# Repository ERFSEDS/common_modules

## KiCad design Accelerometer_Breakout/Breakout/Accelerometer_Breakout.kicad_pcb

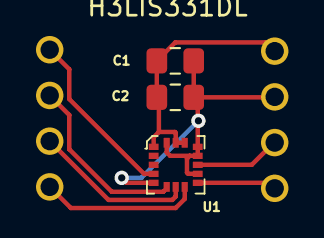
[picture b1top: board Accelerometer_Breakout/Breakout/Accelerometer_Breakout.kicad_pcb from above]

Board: 2 copper layers, 5 parts (0 on the bottom side), 8 nets.

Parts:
C1: 10uF; C_0805_2012Metric_Pad1.15x1.40mm_HandSolder
C2: 0.1uF; C_0805_2012Metric_Pad1.15x1.40mm_HandSolder
U1: H3LIS331DL; TFLGA-16_3x3mm
U2, U3: 4_Pin_header; 4_Pin_Header

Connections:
GND: C1.1, C2.1, U1.5, U1.10, U1.12, U1.13, U1.16, U3.3
unnamed: C1.2, C2.2, U1.1, U1.14, U1.15, U3.4
unnamed: U1.4, U2.1
unnamed: U1.6, U2.2
unnamed: U1.7, U2.3
unnamed: U1.8, U2.4
unnamed: U1.9, U3.1
unnamed: U1.11, U3.2

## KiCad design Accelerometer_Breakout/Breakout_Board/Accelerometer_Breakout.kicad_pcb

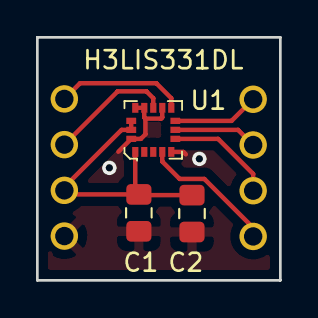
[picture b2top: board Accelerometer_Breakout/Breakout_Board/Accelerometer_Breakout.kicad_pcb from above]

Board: 2 copper layers, 13.5 x 13.5 mm, 5 parts (0 on the bottom side), 8 nets.

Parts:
C1: 10uf; C_0805_2012Metric_Pad1.15x1.40mm_HandSolder
C2: 0.1uf; C_0805_2012Metric_Pad1.15x1.40mm_HandSolder
U1: H3LIS331DL; TFLGA-16_3x3mm
U2, U3: 4_Pin_header; 4_Pin_Header

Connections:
+3V3: C1.1, C2.2, U1.1, U1.14, U1.15, U2.3
/H3LIS331DL_Accelerometer/CS_ACC: U1.8, U3.4
/H3LIS331DL_Accelerometer/INT_1_ACC: U1.11, U2.2
/H3LIS331DL_Accelerometer/INT_2_ACC: U1.9, U2.1
/H3LIS331DL_Accelerometer/SCL_ACC: U1.4, U3.1
/H3LIS331DL_Accelerometer/SDA_ACC: U1.6, U3.2
/H3LIS331DL_Accelerometer/SDO_ACC: U1.7, U3.3
GND: C1.2, C2.1, U1.5, U1.10, U1.12, U1.13, U1.16, U2.4

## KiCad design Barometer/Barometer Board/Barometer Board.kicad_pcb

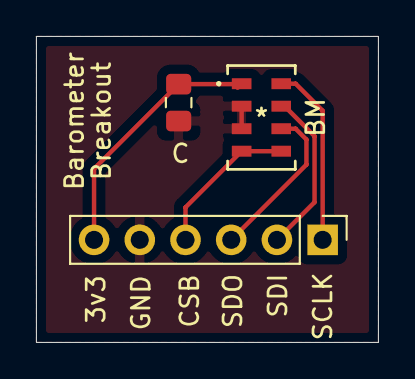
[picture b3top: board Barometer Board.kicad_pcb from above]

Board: 2 copper layers, 19.0 x 17.0 mm, 3 parts (0 on the bottom side), 6 nets.

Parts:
BM: MS560702BA03-50
C: 100nF; C_0805_2012Metric_Pad1.15x1.40mm_HandSolder
Header-Pins301: Conn_01x06_Male; PinHeader_1x06_P2.54mm_Vertical

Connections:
+3V3: BM.1, C.1, Header-Pins301.6
/Barometer/CSB: BM.4, BM.5, Header-Pins301.4
/Barometer/SCLK: BM.8, Header-Pins301.1
/Barometer/SDI: BM.7, Header-Pins301.2
/Barometer/SDO: BM.6, Header-Pins301.3
GND: BM.2, BM.3, C.2, Header-Pins301.5

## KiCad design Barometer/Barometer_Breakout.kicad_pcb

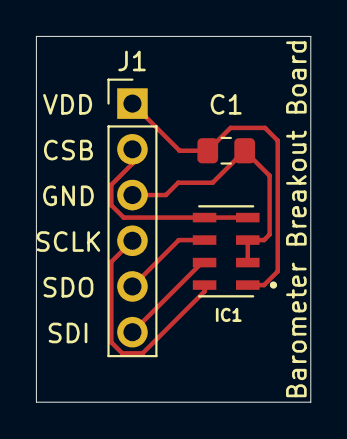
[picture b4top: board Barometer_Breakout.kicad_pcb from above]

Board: 2 copper layers, 15.2 x 20.3 mm, 3 parts (0 on the bottom side), 6 nets.

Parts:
C1: 100nF; C_0805_2012Metric_Pad1.15x1.40mm_HandSolder
IC1: MS560702BA03-50; SON125P300X500X100-8N
J1: Conn_01x06_Male; PinHeader_1x06_P2.54mm_Vertical

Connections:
unnamed: C1.1, IC1.2, IC1.3, J1.3
unnamed: C1.2, IC1.1, J1.1
unnamed: IC1.4, IC1.5, J1.2
unnamed: IC1.8, J1.4
unnamed: IC1.6, J1.5
unnamed: IC1.7, J1.6

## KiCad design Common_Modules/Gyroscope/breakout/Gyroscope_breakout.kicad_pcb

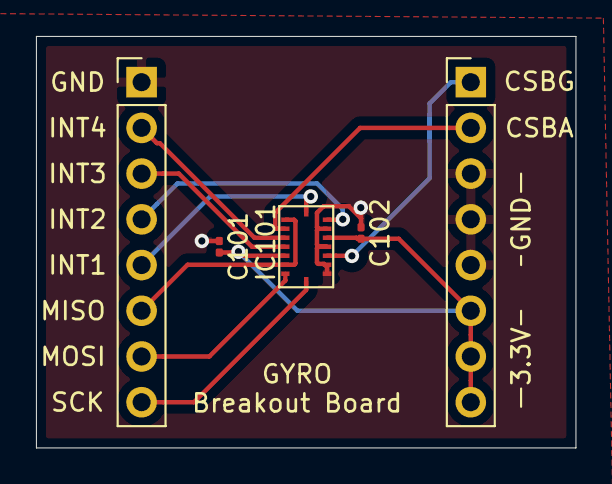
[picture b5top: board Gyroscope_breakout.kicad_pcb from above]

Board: 2 copper layers, 30.0 x 22.9 mm, 5 parts (0 on the bottom side), 11 nets.

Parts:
C101, C102: 100nF; C_0201_0603Metric
IC101: BMI088; 16-LGA-(4.5x3)
J101: Conn_01x08; PinHeader_1x08_P2.54mm_Vertical
e101: Conn_01x08; PinHeader_1x08_P2.54mm_Vertical

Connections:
+3V3: C101.2, C102.2, IC101.3, IC101.11, e101.6, e101.7, e101.8
/CSB_ACCEL: IC101.14, e101.2
/CSB_GYRO: IC101.5, e101.1
/INT1_ACCEL: IC101.16, J101.5
/INT2_ACCEL: IC101.1, J101.4
/INT3_GYRO: IC101.12, J101.3
/INT4_GYRO: IC101.13, J101.2
/MISO: IC101.10, IC101.15, J101.6
/MOSI: IC101.9, J101.7
/SCK: IC101.8, J101.8
GND: C101.1, C102.1, IC101.2, IC101.4, IC101.6, IC101.7, J101.1, e101.3, e101.4, e101.5

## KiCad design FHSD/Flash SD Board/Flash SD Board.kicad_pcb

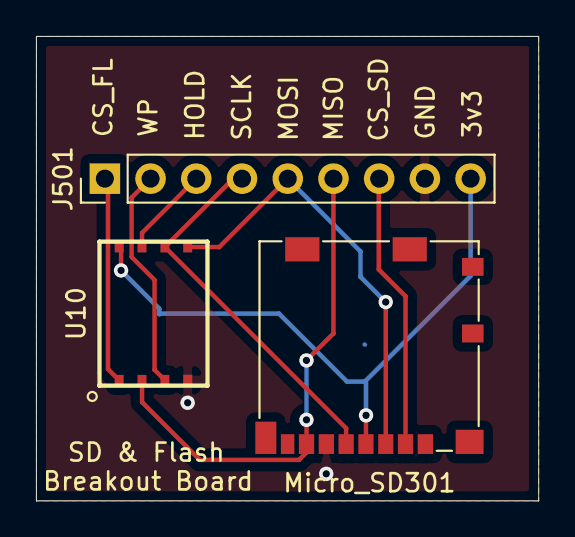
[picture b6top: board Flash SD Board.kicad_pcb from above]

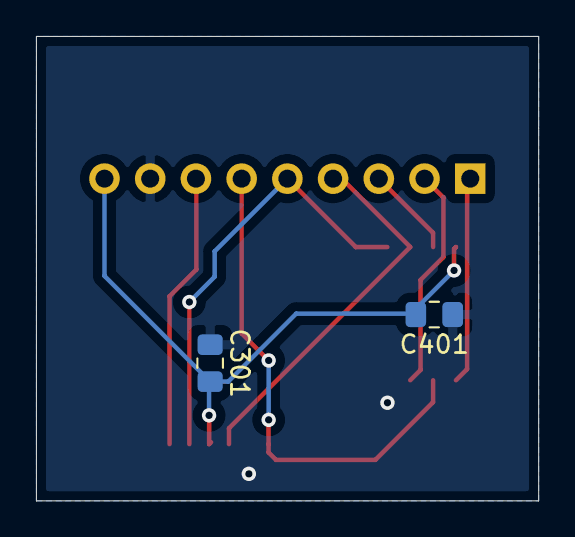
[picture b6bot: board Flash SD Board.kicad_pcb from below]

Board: 2 copper layers, 27.9 x 25.8 mm, 5 parts (2 on the bottom side), 9 nets.

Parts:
C301, C401: 100nF; C_0805_2012Metric_Pad1.15x1.40mm_HandSolder
J501: Conn_01x07_Male; PinHeader_1x09_P2.54mm_Vertical
Micro_SD301: Micro_SD_Card; microSD_HC_Molex_104031-0811
U10: W25N512GVPIT

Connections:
+3V3: C301.2, C401.2, J501.9, Micro_SD301.4, U10.8
/main/Flash Chip/CS_FLASH: J501.1, U10.1
/main/Flash Chip/HOLD: J501.3, U10.7
/main/Flash Chip/MISO: J501.6, Micro_SD301.7, U10.2
/main/Flash Chip/MOSI: J501.5, Micro_SD301.3, U10.5
/main/Flash Chip/SCLK: J501.4, Micro_SD301.5, U10.6
/main/Flash Chip/WP: J501.2, U10.3
/main/Headers/CS_SD: J501.7, Micro_SD301.2
GND: C301.1, C401.1, J501.8, Micro_SD301.6, U10.4

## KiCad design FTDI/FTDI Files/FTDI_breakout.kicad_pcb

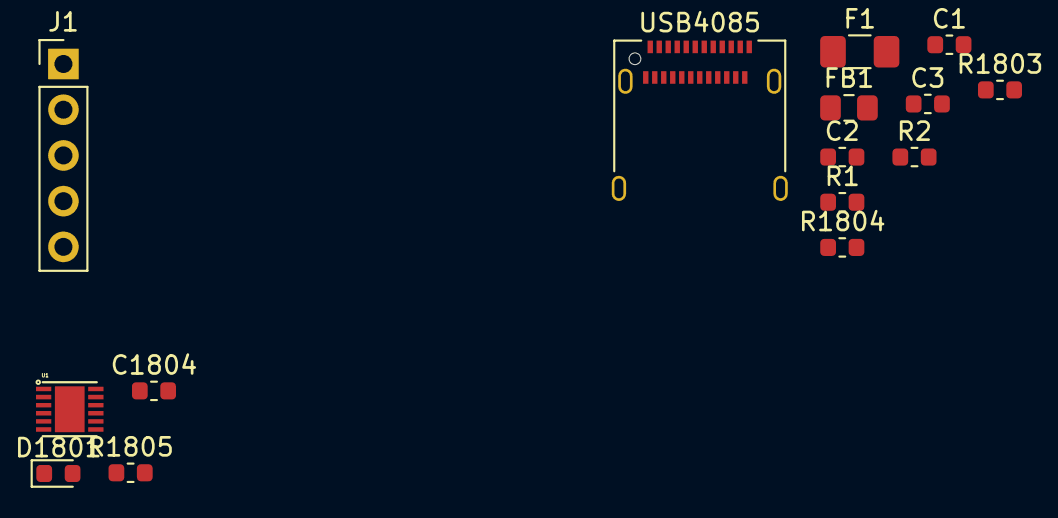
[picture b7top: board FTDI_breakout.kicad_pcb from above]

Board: 2 copper layers, 15 parts (0 on the bottom side), 17 nets, no tracks yet.

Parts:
C1, C2: 47pF; C_0603_1608Metric
C3: 10nF; C_0603_1608Metric
C1804: 100nF; C_0603_1608Metric
D1801: LED; LED_0603_1608Metric
F1: 500mA; Fuse_1206_3216Metric_Pad1.42x1.75mm_HandSolder
FB1: 600 OHM; R_0805_2012Metric_Pad1.15x1.40mm_HandSolder
J1: Conn_01x05_Male; PinHeader_1x05_P2.54mm_Vertical
R1, R2: 27 OHM; R_0603_1608Metric
R1803, R1804: 5k; R_0603_1608Metric
R1805: 270 OHM; R_0603_1608Metric
U1: FT234XD-T; SON45P300X300X80-13N
USB4085: USB_C_Receptacle; USB_C_Receptacle_Amphenol_12401610E4-2A

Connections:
+3V3: C1804.1, R1805.2, U1.2, U1.3, U1.9
/FTDI/CTS: J1.3, U1.11
/FTDI/RTS: J1.4, U1.8
/FTDI/RXD: J1.2, U1.10
/FTDI/TXD: J1.1, U1.7
/FTDI/USBDP: R1.1, U1.12
/USB_C/USBDM: R2.1, U1.1
GND: C1.2, C2.2, C3.1, C1804.2, J1.5, R1803.1, R1804.1, U1.5, U1.13, USB4085.A1, USB4085.A12, USB4085.B1, USB4085.B12, USB4085.S1
unnamed: C1.1, R1.2, USB4085.A6
unnamed: C2.1, R2.2, USB4085.A7
unnamed: C3.2, F1.1, FB1.2
unnamed: D1801.1, U1.6
unnamed: D1801.2, R1805.1
unnamed: F1.2, USB4085.A4, USB4085.A9, USB4085.B4, USB4085.B9
unnamed: R1803.2, USB4085.B5
unnamed: R1804.2, USB4085.A5
VBUS: FB1.1, U1.4

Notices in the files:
parts and their libraries:
Copyright 2016 Accelerated Designs. All rights reserved.
